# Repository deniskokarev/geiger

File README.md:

# Geiger counter project

STM32 microcontroller project measuring radioation. Using

- STM32 Nucleo board
- STM X-Nucleo IDB05A2 bluetooth shield
- SBM-20 tube

**NB** using STM submodules, so checkout in `git clone --recursive` fashion.

The hardware is in the Nucleo (Arduino) shield form-factor

Exporting the readings over Blutooth to a Wearable Android client.

- [Hardware](./hardware) DipTrace schematics and layout for high-voltage and sensor shield
- [Firmware](./firmware) CubeMX + CLion project
- [Wearable Client](./client/android) Android Studio project for wearable client

Inspired by [Mighty Ohm Geiger kit](https://mightyohm.com/blog/products/geiger-counter/)

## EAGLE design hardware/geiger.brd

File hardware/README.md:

# Geiger counter shield

The high-voltage supply is based on ~4kHz PWM signal coming from MC. PWM signal constantly running, but the high-voltage transistor is not. There is an OpAmp-based voltage sensor, which suppresses PWM and saves energy. 

It makes about ~3 PWM impulses per second sustaining ~400V with minimal effort.

DipTrace was used to compose schematic and board layout.

There are Eagle schematics and board files attached as well.

Also, LTSpice simulation file with opamp feedback loop calculations.

**TODO**

The voltage sensor is using BJT transistor as the first stage, which is very temperature sensitive. Must rework the schematic to avoid relying on the transistor.

MC gets EXTI interrupts on voltage below - this occrs about once a second so we can turn PWM timer off entirely.

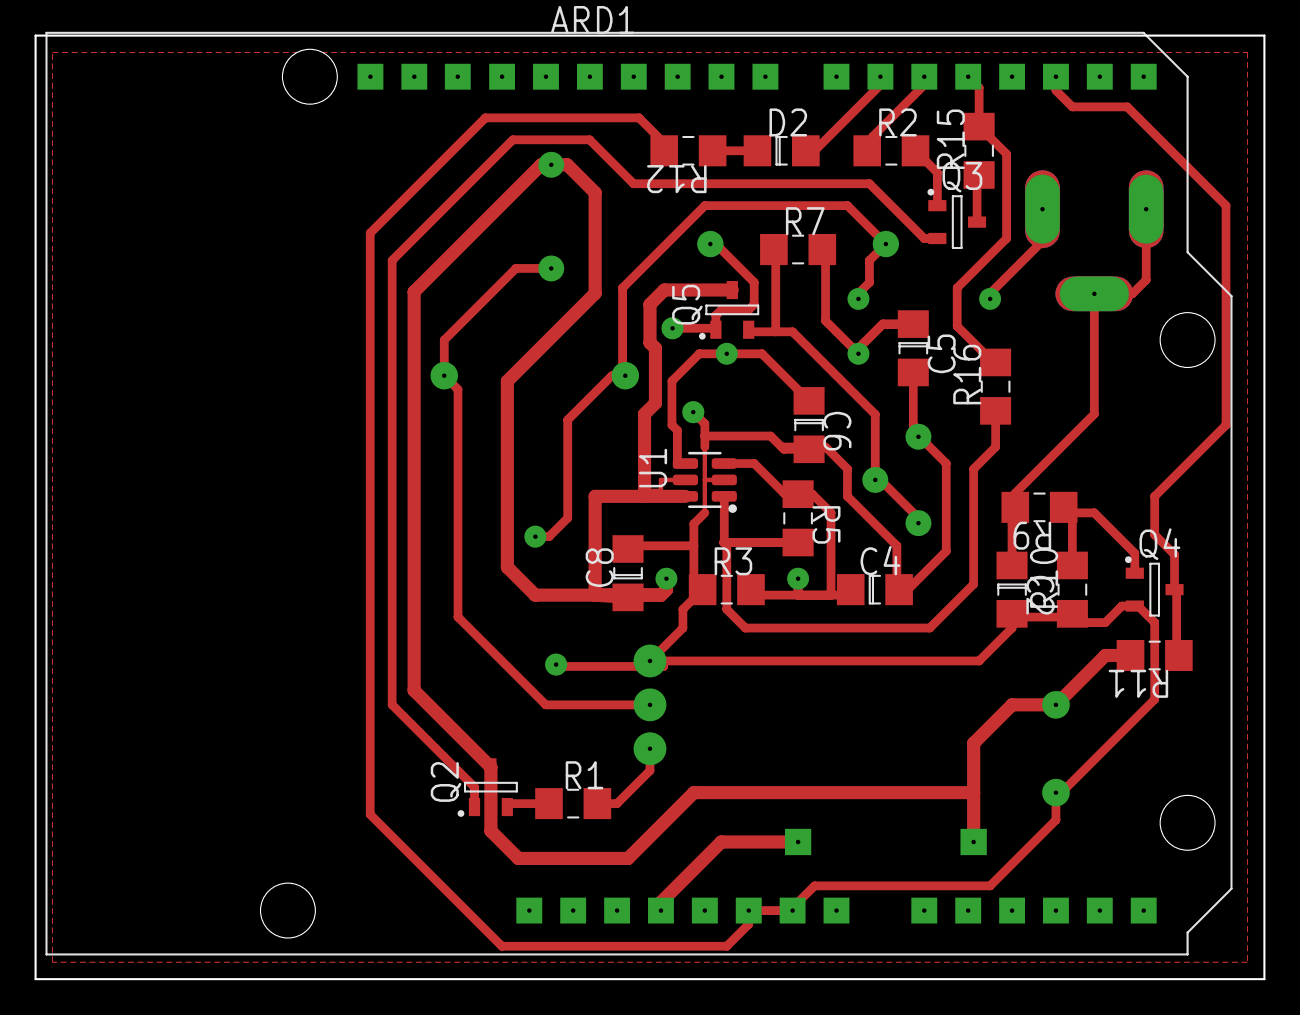
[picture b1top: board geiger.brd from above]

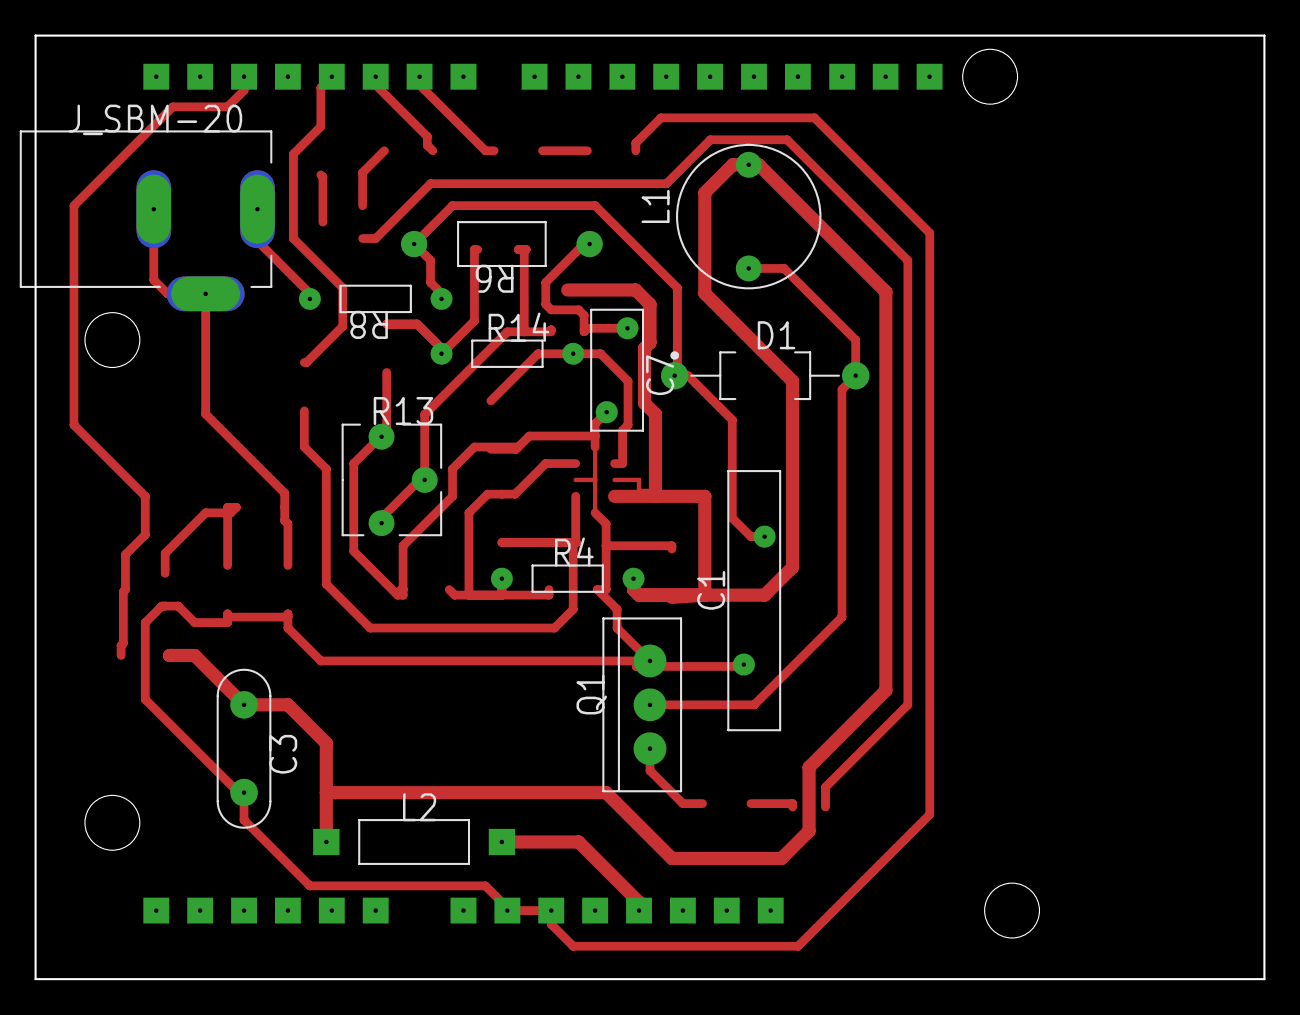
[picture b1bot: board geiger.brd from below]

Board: 2 copper layers, 71.1 x 54.6 mm, 36 parts (13 on the bottom side), 24 nets.

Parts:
ARD1: ARDUINO UNO; ADRUINO_UNO
C1: .005u; CAPRB740W60L1500T300H1800
C2: 220pF; CAP_1206
C3: 220u; CAP-5.08/9.15x3
C4: 104; CAP_1206
C5, C6: 1n; CAP_1206
C7: 0.1uF; CAPRB485W60L700T300H1000
C8: 1u; CAP_1206
D1: 1N4937G; DIOAD1048W78L520D270_AD2
D2: LED_1206; DIO_1206
J_SBM-20: 644456-2; 4840-2211
L1: 6100-103K-RC; BOURNS_6100-100K
L2: 100nH; IND_400
Q1: FJP5027RTU; TO-220
Q2, Q3, Q4, Q5: MMBT3904; SOT23
R1, R12: 220; RES_1206
R2, R3, R10: 100k; RES_1206
R4: 100k; RES-7.62/4x1.5
R5: 10M; RES_1206
R6: 5GOhm; RES-10.16/5.1x2.5
R7: 1M; RES_1206
R8: 4.7M; RES-7.62/4x1.5
R9: 22k; RES_1206
R11: 10k; RES_1206
R13: 500k; 306X
R14: 1M; RES-7.62/4x1.5
R15: 1k; RES_1206
R16: 1; RES_1206
U1: OPA341NA; SOT23-6P95_270X145L35X35M

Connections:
CTL: R5.2, R16.1, U1.1
GND: ARD1.GND2, ARD1.GND3, C1.1, C2.2, C3.2, C4.2, C5.2, C6.2, C7.2, C8.2, Q1.3, Q4.2, R3.1, R10.1, R12.2, R13.1, U1.2
HI: J_SBM-20.1, R8.2
HI_DANGER: C1.2, D1.1, R6.2, R8.1
Half_With_Histeresis: C4.1, R3.2, R4.1, R5.1, U1.3
Hi_Sensor: C6.1, R14.2, U1.4
NOUT: ARD1.2, Q4.3, R11.1
Net_2: D1.2, L1.1, Q1.2
Net_3: Q2.1, Q3.2
Net_4: Q1.1, R1.2
Net_5: Q2.2, R1.1
Net_6: Q3.1, R2.2
Net_11: C7.1, Q5.1, R6.1
Net_12: C2.1, J_SBM-20.2, J_SBM-20.3, R9.2
Net_13: Q4.1, R9.1, R10.2
Net_16: ARD1.3.3V, L2.2
Net_17: D2.1, R12.1
Net_18: ARD1.6, D2.2
Net_20: C5.1, R7.2, R14.1
Net_21: Q5.2, R7.1, R13.2, R13.3
Net_22: Q3.3, R15.1
Net_23: ARD1.4, R15.2, R16.2
PWM: ARD1.5, R2.1
VCC: C3.1, C8.1, L1.2, L2.1, Q2.3, Q5.3, R4.2, R11.2, U1.5, U1.6

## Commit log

2022-05-08 initial CubeMX project
2022-05-08 fixing my ARM toolchain path
2022-05-08 removing cmake build dir
2022-05-08 adding gitignore
2022-05-09 adding OCD geiger debug config
2022-05-09 fixing CubeMX config for the board
2022-05-09 fixing SPI1 and re-rendering
2022-05-10 changing CubeMX BlueNRG project to SensorDemo
2022-05-10 adding rendered code
2022-05-14 !!! working bluenrg sensor demo
2022-05-22 Add TIM4 1Hz timer
2022-05-22 Add geiger counter EXTI
2022-05-22 Make time_since_boot in milliseconds
2022-05-22 Calculate simple CPM
2022-05-23 Populate CPM over ST BLE as pressure
2022-06-20 Add PWM output, remove unused timer
2022-06-25 temporarily forcing CTL signal to Hi
2022-07-01 Added Geiger_New sensor pin PA10
2022-07-01 making PWM 4kHz
2022-07-04 Add LED 0.1sec blink on the geiger counter event
2022-07-04 adding comments for LED blink
2022-07-04 working version
2022-07-04 adding DS_Store to gitignore
2022-07-04 Moved firmware code to its own dir
2022-07-04 moving to firmware dir
2022-07-04 moving CLion project to firmware dir
2022-07-04 adding Android Client app
2022-07-04 working client
2022-07-04 removing unused files
2022-07-04 Adding readme files
2022-07-04 formatting
2022-07-04 adding Eagle schematics and board
2024-06-02 adding pwm functionality to Zephyr fw
2024-06-02 zfirm adding boost_on gpio
2024-06-02 zfirm set resonant freq of 200kHz
